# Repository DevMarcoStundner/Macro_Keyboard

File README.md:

# Macro Keyboard GUI

## Behaviour
  The GUI should display 9 buttons in the center which represents the buttons from the keyboard.
  If one of the buttons gets clicked there will be a label underneath which displays the saved shortcut.
  Below that there will be an entry were the user can input the desired shortcut.
  On the other side of the window ther will be two extra buttons.
  On of them will save the newly inputed shortcut.
  The other one will connect the GUI to the Marco-Keyboard.
  The inputed shortcuts will also gets saved in an external file because there is no dedicated memory for that.
  Besides that the GUI also has to deal with the USB-Connectivity.

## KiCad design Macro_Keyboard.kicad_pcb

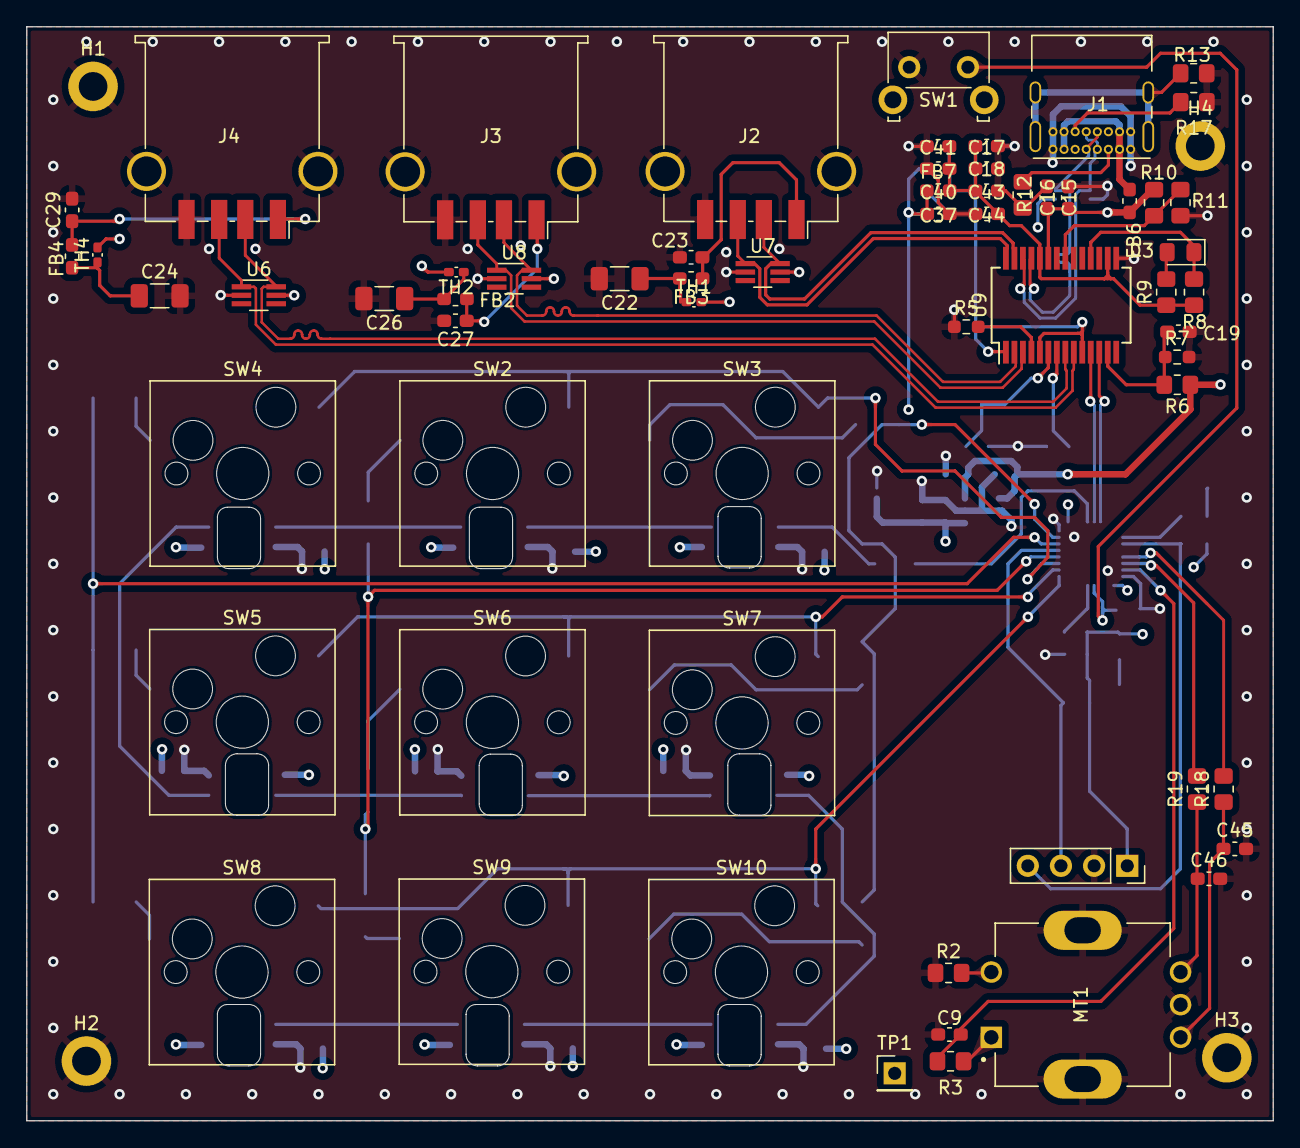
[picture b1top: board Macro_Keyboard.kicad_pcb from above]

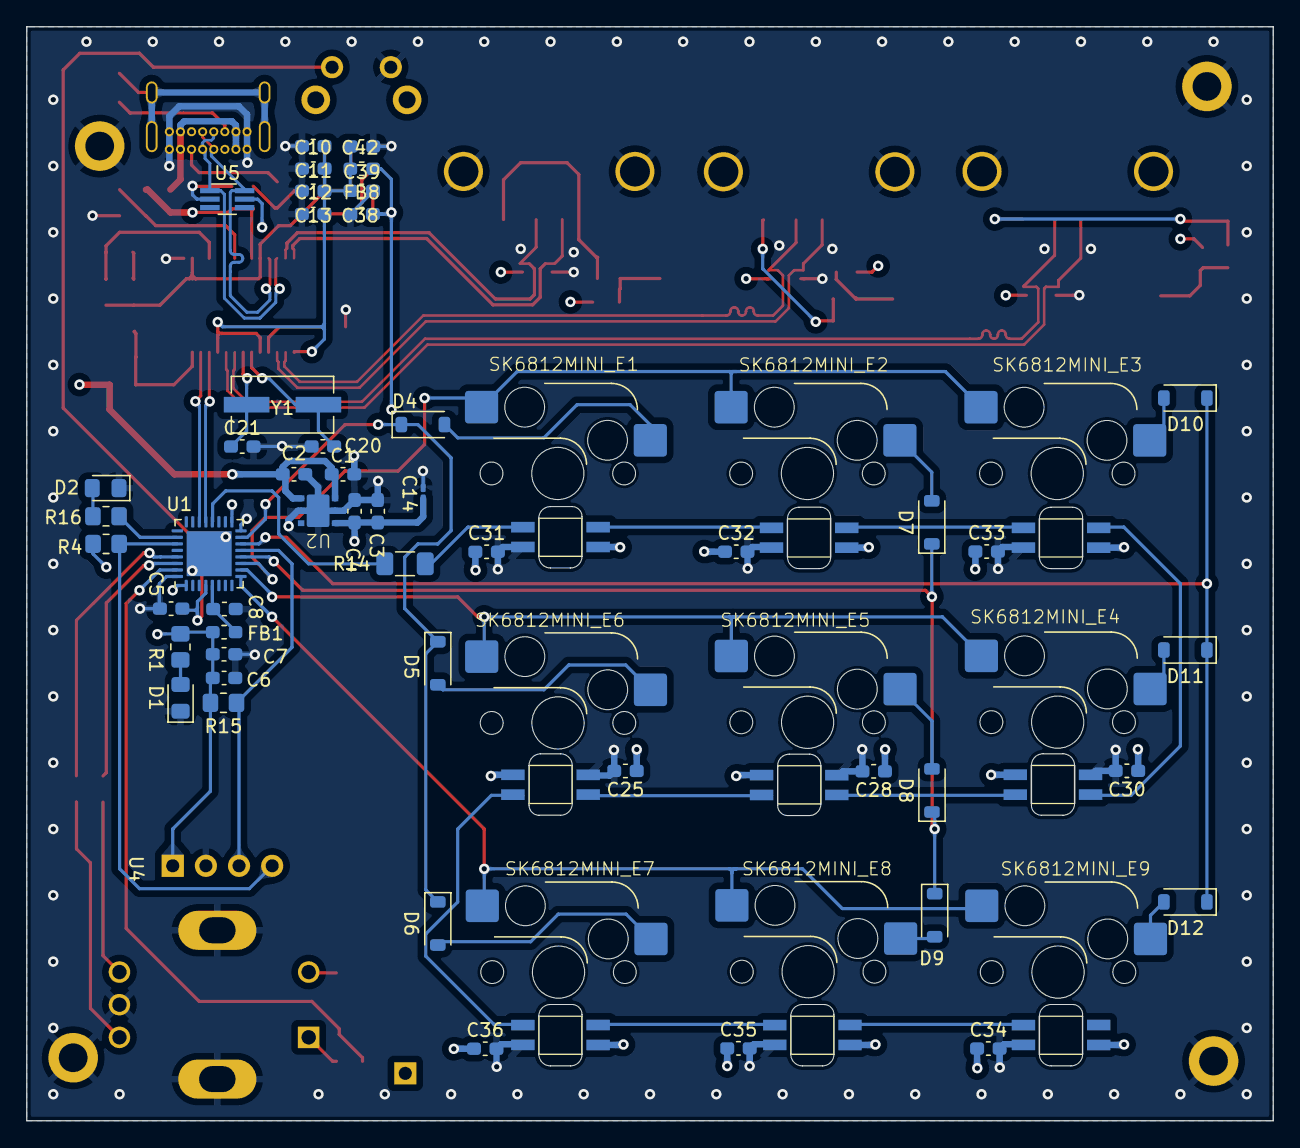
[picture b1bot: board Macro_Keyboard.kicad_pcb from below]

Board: 4 copper layers, 95.5 x 83.8 mm, 125 parts (58 on the bottom side), 71 nets.

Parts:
C1, C4, C5, C6, C7, C8: 100nF; C_0603_1608Metric_Pad1.08x0.95mm_HandSolder
C2, C3, C16, C37, C38, C39, C40: 1uF; C_0603_1608Metric_Pad1.08x0.95mm_HandSolder
C9, C10, C11, C12, C13, C15, C17, C18, C19, C41, C42, C43, C44, C45, C46: 0.1uF; C_0603_1608Metric_Pad1.08x0.95mm_HandSolder
C14: 10uF; C_0201_0603Metric_Pad0.64x0.40mm_HandSolder
C20, C21: 20pF; C_0603_1608Metric_Pad1.08x0.95mm_HandSolder
C22, C24, C26: 100uF/10V; C_1206_3216Metric_Pad1.33x1.80mm_HandSolder
C23, C27, C29: 0.1uF/10V; C_0603_1608Metric_Pad1.08x0.95mm_HandSolder
C25, C28, C30, C31, C32, C33, C34, C35, C36: tbd; C_0603_1608Metric_Pad1.08x0.95mm_HandSolder
D1, D2, D3: LED; LED_0805_2012Metric_Pad1.15x1.40mm_HandSolder
D4, D5, D6, D7, D8, D9, D10, D11, D12: D_Small; D_SOD-123
FB1, FB2, FB3, FB4, FB6, FB7, FB8: BLM18BA; L_0603_1608Metric_Pad1.05x0.95mm_HandSolder
H1, H2, H3, H4: MountingHole_Pad; MountingHole_2.2mm_M2_DIN965_Pad
J1: USB_C_Receptacle_USB2.0; USB_C_Receptacle_GCT_USB4085
J2, J3, J4: USB_A; USB_A_TE_292303-7_Horizontal
MT1: PEC11R-4215F-S0024; XDCR_PEC11R-4215F-S0024
R1, R4: 510; R_0805_2012Metric_Pad1.20x1.40mm_HandSolder
R2, R3, R6, R10, R18, R19: 10k; R_0805_2012Metric_Pad1.20x1.40mm_HandSolder
R5: 680; R_0603_1608Metric_Pad0.98x0.95mm_HandSolder
R7: 47k; R_0603_1608Metric_Pad0.98x0.95mm_HandSolder
R8: 100k; R_0805_2012Metric_Pad1.20x1.40mm_HandSolder
R9: 470; R_0805_2012Metric_Pad1.20x1.40mm_HandSolder
R11: 20k; R_0805_2012Metric_Pad1.20x1.40mm_HandSolder
R12, R17: 5.11k; R_0805_2012Metric_Pad1.20x1.40mm_HandSolder
R13: 1M; R_0805_2012Metric_Pad1.20x1.40mm_HandSolder
R14: 500; R_1206_3216Metric_Pad1.30x1.75mm_HandSolder
R15, R16: 4.7k; R_0805_2012Metric_Pad1.20x1.40mm_HandSolder
SK6812MINI_E1, SK6812MINI_E2, SK6812MINI_E3, SK6812MINI_E4, SK6812MINI_E5, SK6812MINI_E6, SK6812MINI_E7, SK6812MINI_E8, SK6812MINI_E9: SK6812_Mini
SW1: SW_Push; SW_Tactile_SKHH_Angled
SW2, SW3, SW4, SW5, SW6, SW7, SW8, SW9, SW10: SW_DIP_x01; SW_Hotswap_Kailh_MX_1.00u
TH1, TH2, TH4: 500mA/6V; Fuse_0402_1005Metric_Pad0.77x0.64mm_HandSolder
TP1: TestPoint; PinHeader_1x01_P2.54mm_Vertical
U1: STM32L432KCUx; QFN-32-1EP_5x5mm_P0.5mm_EP3.45x3.45mm
U2: LD39050PU33R; LD39050_DFN6
U4: PinSocket_1x04_P2.54mm_Vertical
U5, U6, U7, U8: NUP2202; SOT-363_SC-70-6_Handsoldering
U9: SSOP-28_5.3x10.2mm_P0.65mm
Y1: 12MHz; Crystal_SMD_ECS_CSM3X-2Pin_7.6x4.1mm

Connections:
+3.3V: C3.1, C4.1, C6.1, C7.1, C14.1, C37.1, C38.1, FB1.1, FB7.1, FB8.1, R1.1, R15.1, R16.1, U1.1 (VDD), U1.17 (VDD), U2.4 (V_{OUT}), U4.1 (VDD)
+5V: C1.1, C2.1, C15.1, C16.1, C25.1, C28.1, C30.1, C31.1, C32.1, C33.1, C34.1, C35.1, C36.1, FB6.2, R6.1, R10.1, SK6812MINI_E1.1 (VDD), SK6812MINI_E2.1 (VDD), SK6812MINI_E3.1 (VDD), SK6812MINI_E4.1 (VDD), SK6812MINI_E5.1 (VDD), SK6812MINI_E6.1 (VDD), SK6812MINI_E7.1 (VDD), SK6812MINI_E8.1 (VDD), SK6812MINI_E9.1 (VDD), TH1.2, TH2.2, TH4.2, TP1.1, U2.1 (EN), U2.6 (V_{IN}), U5.5, U6.5, U7.5, U8.5, U9.23 (V5)
/USB/AVDD: C10.2, C11.2, C12.2, C13.2, C39.1, C42.2, FB8.2, U9.1 (AVDD), U9.5 (AVDD), U9.10 (AVDD)
/USB/DVDD: C17.2, C18.2, C40.1, C41.2, C43.2, C44.2, FB7.2, R8.1, R9.1, U9.16 (DVDD), U9.24 (V33)
/USB/D_N0: J1.A7 (D-), J1.B7 (D-), U5.6, U9.25 (DM0)
/USB/D_N1: J2.2 (D-), U7.6, U9.27 (DM1)
/USB/D_N2: J3.2 (D-), U8.6, U9.2 (DM2)
/USB/D_N3: J4.2 (D-), U6.6, U9.8 (DM3)
/USB/D_P0: J1.A6 (D+), J1.B6 (D+), U5.1, U9.26 (DP0)
/USB/D_P1: J2.3 (D+), U7.1, U9.28 (DP1)
/USB/D_P2: J3.3 (D+), U8.1, U9.3 (DP2)
/USB/D_P3: J4.3 (D+), U6.1, U9.9 (DP3)
/USB/OVERCUR1: R10.2, R11.1, U9.21 (OVCUR1)
/USB/PGANG: D3.1 (K), R8.2, U9.18 (PGANG)
/USB/RESET: C19.1, R6.2, R7.1, U9.13 (RESET)
/USB/X1: C20.1, U9.6 (X1), Y1.1
/USB/X2: C21.1, U9.7 (X2), Y1.2
BOOT: MT1.1, R3.1
COL 0: D10.1 (K), D11.1 (K), D12.1 (K), U1.14 (PB0)
COL 1: D7.1 (K), D8.1 (K), D9.1 (K), U1.12 (PA6)
COL 2: D4.1 (K), D5.1 (K), D6.1 (K), U1.15 (PB1)
GND: C1.2, C2.2, C3.2, C4.2, C5.2, C6.2, C7.2, C8.2, C9.2, C10.1, C11.1, C12.1, C13.1, C14.2, C15.2, C16.2, C17.1, C18.1, C19.2, C20.2, C21.2, C22.2, C23.2, C24.2, C25.2, C26.2, C27.2, C28.2, C29.2, C30.2, C31.2, C32.2, C33.2, C34.2, C35.2, C36.2, C37.2, C38.2, C39.2, C40.2, C41.1, C42.1, C43.1, C44.1, C45.2, C46.2, D1.1 (K), D2.1 (K), H1.1, H2.1, H3.1, H4.1, J1.A1 (GND), J1.A12 (GND), J1.B1 (GND), J1.B12 (GND), J2.4 (GND), J2.5 (Shield), J3.4 (GND), J3.5 (Shield), J4.4 (GND), J4.5 (Shield), MT1.COM, MT1.S1 (SHIELD), MT1.S2 (SHIELD), R2.1, R5.1, R7.2, R11.2, R12.2, R13.2, R17.2, SK6812MINI_E1.3 (VSS), SK6812MINI_E2.3 (VSS), SK6812MINI_E3.3 (VSS), SK6812MINI_E4.3 (VSS), SK6812MINI_E5.3 (VSS), SK6812MINI_E6.3 (VSS), SK6812MINI_E7.3 (VSS), SK6812MINI_E8.3 (VSS), SK6812MINI_E9.3 (VSS), SW1.1, U1.16 (VSS), U1.32 (VSS), U1.33 (VSS), U2.2 (GND), U2.5 (GND), U2.GND, U4.2 (GND), U5.2, U6.2, U7.2, U8.2, U9.15 (GND)
LED: R14.1, U1.20 (PA10)
unnamed: C22.1, FB3.2, TH1.1
unnamed: C24.1, FB4.2, TH4.1
unnamed: C26.1, FB2.2, TH2.1
unnamed: C45.1, MT1.A, R18.1
unnamed: C46.1, MT1.B, R19.1
unnamed: D1.2 (A), R1.2
unnamed: D2.2 (A), R4.2
unnamed: D3.2 (A), R9.2
unnamed: D4.2 (A), SW3.1
unnamed: D5.2 (A), SW7.1
unnamed: D6.2 (A), SW10.1
unnamed: D7.2 (A), SW2.1
unnamed: D8.2 (A), SW6.1
unnamed: D9.2 (A), SW9.1
unnamed: D10.2 (A), SW4.1
unnamed: D11.2 (A), SW5.1
unnamed: D12.2 (A), SW8.1
unnamed: FB6.1, J1.A4 (VBUS), J1.A9 (VBUS), J1.B4 (VBUS), J1.B9 (VBUS)
unnamed: J1.A5 (CC1), R12.1
unnamed: J1.B5 (CC2), R17.1
unnamed: J1.S1 (SHIELD), R13.1
unnamed: C23.1, FB3.1, J2.1 (VBUS)
unnamed: C27.1, FB2.1, J3.1 (VBUS)
unnamed: C29.1, FB4.1, J4.1 (VBUS)
unnamed: MT1.2, R2.2
unnamed: R14.2, SK6812MINI_E1.4 (DIN)
unnamed: SK6812MINI_E1.2 (DOUT), SK6812MINI_E2.4 (DIN)
unnamed: SK6812MINI_E2.2 (DOUT), SK6812MINI_E3.4 (DIN)
unnamed: SK6812MINI_E3.2 (DOUT), SK6812MINI_E4.4 (DIN)
unnamed: SK6812MINI_E4.2 (DOUT), SK6812MINI_E5.4 (DIN)
unnamed: SK6812MINI_E5.2 (DOUT), SK6812MINI_E6.4 (DIN)
unnamed: SK6812MINI_E6.2 (DOUT), SK6812MINI_E7.4 (DIN)
unnamed: SK6812MINI_E7.2 (DOUT), SK6812MINI_E8.4 (DIN)
unnamed: SK6812MINI_E8.2 (DOUT), SK6812MINI_E9.4 (DIN)
unnamed: C5.1, SW1.2, U1.4 (NRST)
unnamed: R4.1, U1.26 (PB3)
unnamed: C9.1, R3.2, U1.31 (PH3)
unnamed: R5.2, U9.4 (RREF)
ROW 0: SW2.2, SW3.2, SW4.2, U1.11 (PA5)
ROW 1: SW5.2, SW6.2, SW7.2, U1.10 (PA4)
ROW 2: SW8.2, SW9.2, SW10.2, U1.9 (PA3)
Rotary_A: R18.2, U1.29 (PB6)
Rotary_B: R19.2, U1.30 (PB7)
SCK: R15.2, U1.13 (PA7), U4.3 (SCK)
SDA: R16.2, U1.27 (PB4), U4.4 (SDA)
USBD_N: U1.21 (PA11), U9.11 (DM4)
USBD_P: U1.22 (PA12), U9.12 (DP4)
VDDA: C8.1, FB1.2, U1.5 (VDDA)

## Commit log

2023-04-24 Schematic fertig und Layout gerouted
2023-04-25 Neue Anordnung für bessere Usb Leitungen
2023-10-20 Started with HID GUI
    Keyboard buttons are implemented but not right placed
2023-10-20 Changed type of placeing
2024-01-20 Add first Freecad element
2024-01-20 Pad finished without Pocket
2024-01-20 Pad now with Pocket
2024-01-23 Add cut-out for input
2024-01-23 started with drill hole
2024-01-29 Add Zylinder but cant add hole
2024-01-29 Add Zylinder with holes
2024-01-29 Made walls thiner
2024-03-07 Add STM32 Symbol and changed schematic
